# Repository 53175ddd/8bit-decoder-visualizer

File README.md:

# 8bit-decoder-visualizer

基板イメージ

動作イメージ（YouTube に飛びます）

## 部品表

| 部品番号 | 部品名 | 個数 | リンク |
|:----|:----|----:|:----|
| C1 | 0.1uF 1608M | 1 | [113374](<https://akizukidenshi.com/catalog/g/g113374/>) |
| D1 ~ D8 | LED 5mm | 8 | [112605](<https://akizukidenshi.com/catalog/g/g112605/>) |
| D9 ~ D16 | 1N4148W SOD-123F | 8 | [g116985](<https://akizukidenshi.com/catalog/g/g116985/>) |
| R1 ~ R8 | 1kΩ 1608M | 8 | [130351](<https://akizukidenshi.com/catalog/g/g130351/>) |
| R9 ~ R12 | 10kΩ 1608M | 4 | [130355](<https://akizukidenshi.com/catalog/g/g130355/>) |
| SW1 ~ SW8 | SPDT トグルスイッチ | 8 | [100300](<https://akizukidenshi.com/catalog/g/g100300/>) |
| U1 ~ U6 | 7 セグメント LED モジュール | 6 | [110360](<https://akizukidenshi.com/catalog/g/g110360/>) |
| U7 | 74HC595 | 1 | [131760](<https://akizukidenshi.com/catalog/g/g131760/>) |
| U8 | Seeed XIAO | 1 | [117044](<https://akizukidenshi.com/catalog/g/g117044/>) |

---

<a href="https://github.com/53175ddd/8bit-decoder-visualizer">This work</a> is licensed under <a href="https://creativecommons.org/licenses/by-sa/4.0/">CC BY-SA 4.0</a></br>

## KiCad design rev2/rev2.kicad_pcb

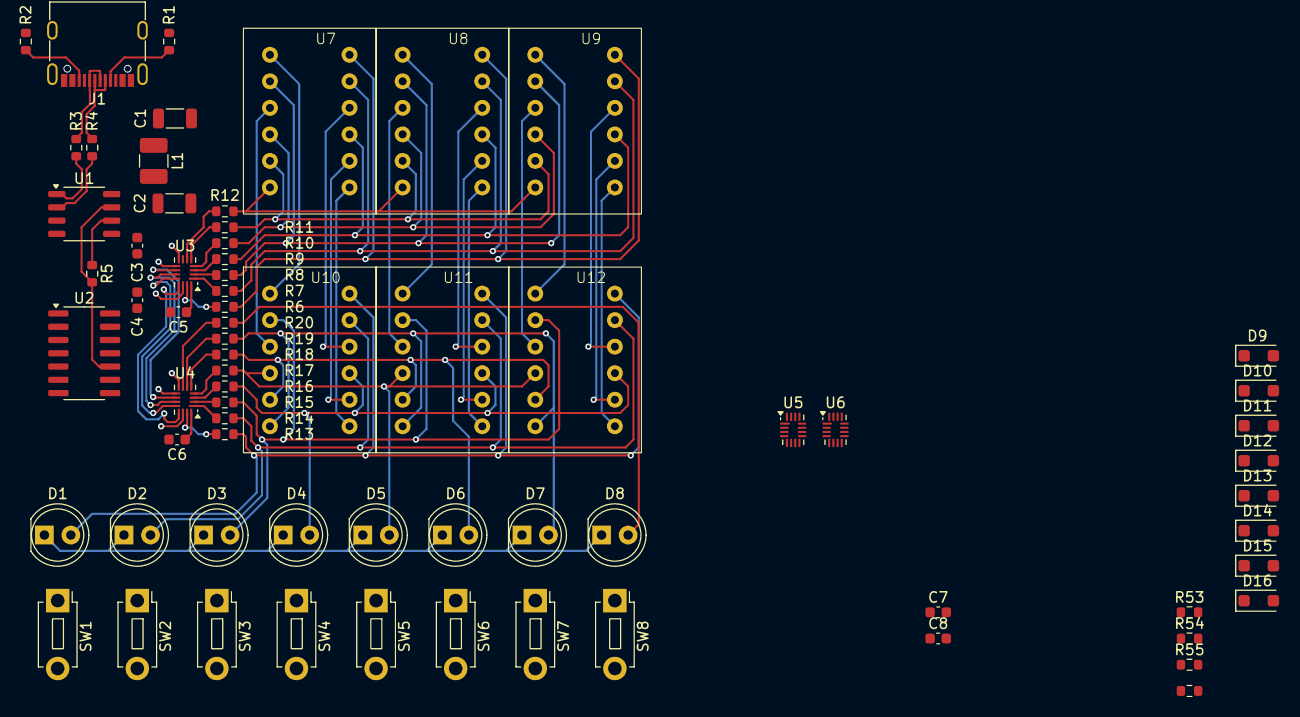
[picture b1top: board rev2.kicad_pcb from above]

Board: 2 copper layers, 70 parts (0 on the bottom side), 78 nets.

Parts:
C1, C2: 10uF; L_1206_3216Metric
C3, C4, C5, C6, C7, C8: 0.1uF; C_0603_1608Metric
D1, D2, D3, D4, D5, D6, D7, D8: LED; LED_D5.0mm
D9, D10, D11, D12, D13, D14, D15, D16: D; D_SOD-123F
J1: USB_C_Receptacle_USB2.0_14P; USB_C_Receptacle_G-Switch_GT-USB-7010ASV
L1: 1.5uH; L_1210_3225Metric_Pad1.42x2.65mm_HandSolder
R1, R2: 5.1k; R_0603_1608Metric
R3, R4: 22; R_0603_1608Metric
R5, R6, R7, R8, R9, R10, R11, R12, R13, R14, R15, R16, R17, R18, R19, R20: 1k; R_0603_1608Metric
R53, R54, R55, R56: 10k; R_0603_1608Metric
SW1, SW2, SW3, SW4, SW5, SW6, SW7, SW8: SW_Push; SW_PUSH_1P1T_6x3.5mm_H4.3_APEM_MJTP1243
U1: CH340N; SOP-8_3.9x4.9mm_P1.27mm
U2: ATtiny1604-SS; SOIC-14_3.9x8.7mm_P1.27mm
U3, U4, U5, U6: 74HC595; UQFN-16_1.8x2.6mm_P0.4mm
U7, U8, U9, U10, U11, U12: C-2570SR

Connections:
+5V: C2.1, C3.1, C4.1, C5.1, C6.1, C7.1, C8.1, L1.2, R53.1, R54.1, R55.1, R56.1, U1.5 (VCC), U2.1 (VCC), U3.16 (VCC), U4.16 (VCC), U5.16 (VCC), U6.16 (VCC)
/DN: R4.2, U1.2 (UD-)
/DP: R3.2, U1.1 (UD+)
/HC595_CLEAR: U3.10 (~SRCLR), U4.10 (~SRCLR), U5.10 (~SRCLR), U6.10 (~SRCLR)
/HC595_CLOCK: U3.11 (SRCLK), U4.11 (SRCLK), U5.11 (SRCLK), U6.11 (SRCLK)
/HC595_EN: U3.13 (~OE), U4.13 (~OE), U5.13 (~OE), U6.13 (~OE)
/HC595_LATCH: U3.12 (RCLK), U4.12 (RCLK), U5.12 (RCLK), U6.12 (RCLK)
/READ_0: R53.2, SW1.2, SW5.2
/READ_1: R54.2, SW2.2, SW6.2
/READ_2: R55.2, SW3.2, SW7.2
/READ_3: R56.2, SW4.2, SW8.2
/SCAN_0: D9.1 (K), D10.1 (K), D11.1 (K), D12.1 (K)
/SCAN_1: D13.1 (K), D14.1 (K), D15.1 (K), D16.1 (K)
/SOURCE_1A: R6.2, U7.12 (ROW1), U8.12 (ROW1), U9.12 (ROW1)
/SOURCE_1B: R7.2, U7.11 (ROW2), U8.11 (ROW2), U9.11 (ROW2)
/SOURCE_1C: R8.2, U7.2 (ROW3), U8.2 (ROW3), U9.2 (ROW3)
/SOURCE_1D: R9.2, U7.9 (ROW4), U8.9 (ROW4), U9.9 (ROW4)
/SOURCE_1E: R10.2, U7.4 (ROW5), U8.4 (ROW5), U9.4 (ROW5)
/SOURCE_1F: R11.2, U7.5 (ROW6), U8.5 (ROW6), U9.5 (ROW6)
/SOURCE_1G: R12.2, U7.6 (ROW7), U8.6 (ROW7), U9.6 (ROW7)
/SOURCE_2A: D1.2 (A), R13.2, U10.12 (ROW1), U11.12 (ROW1), U12.12 (ROW1)
/SOURCE_2B: D2.2 (A), R14.2, U10.11 (ROW2), U11.11 (ROW2), U12.11 (ROW2)
/SOURCE_2C: D3.2 (A), R15.2, U10.2 (ROW3), U11.2 (ROW3), U12.2 (ROW3)
/SOURCE_2D: D4.2 (A), R16.2, U10.9 (ROW4), U11.9 (ROW4), U12.9 (ROW4)
/SOURCE_2E: D5.2 (A), R17.2, U10.4 (ROW5), U11.4 (ROW5), U12.4 (ROW5)
/SOURCE_2F: D6.2 (A), R18.2, U10.5 (ROW6), U11.5 (ROW6), U12.5 (ROW6)
/SOURCE_2G: D7.2 (A), R19.2, U10.6 (ROW7), U11.6 (ROW7), U12.6 (ROW7)
/SOURCE_2H: D8.2 (A), R20.2
/UPDI: R5.2, U1.7 (RXD), U2.10 (~RESET/PA0)
/USB_PLUG_DN: J1.A7 (D-), J1.B7 (D-), R4.1
/USB_PLUG_DP: J1.A6 (D+), J1.B6 (D+), R3.1
GND: C1.2, C2.2, C3.2, C4.2, C5.2, C6.2, C7.2, C8.2, J1.A1 (GND), J1.A12 (GND), J1.B1 (GND), J1.B12 (GND), J1.S1 (SHIELD), R1.2, R2.2, U1.3 (GND), U2.14 (GND), U3.8 (GND), U4.8 (GND), U5.8 (GND), U6.8 (GND)
unnamed: D1.1 (K), D2.1 (K), D3.1 (K), D4.1 (K), D5.1 (K), D6.1 (K), D7.1 (K), D8.1 (K)
unnamed: D9.2 (A), SW1.1
unnamed: D10.2 (A), SW2.1
unnamed: D11.2 (A), SW3.1
unnamed: D12.2 (A), SW4.1
unnamed: D13.2 (A), SW5.1
unnamed: D14.2 (A), SW6.1
unnamed: D15.2 (A), SW7.1
unnamed: D16.2 (A), SW8.1
unnamed: J1.A5 (CC1), R1.1
unnamed: J1.B5 (CC2), R2.1
unnamed: U7.1 (COL1), U10.1 (COL1)
unnamed: U7.3 (COL2), U10.3 (COL2)
unnamed: U7.10 (COL3), U10.10 (COL3)
unnamed: U7.7 (COL4), U10.7 (COL4)
unnamed: U7.8 (COL5), U10.8 (COL5)
unnamed: U8.1 (COL1), U11.1 (COL1)
unnamed: U8.3 (COL2), U11.3 (COL2)
unnamed: U8.10 (COL3), U11.10 (COL3)
unnamed: U8.7 (COL4), U11.7 (COL4)
unnamed: U8.8 (COL5), U11.8 (COL5)
unnamed: U9.1 (COL1), U12.1 (COL1)
unnamed: U9.3 (COL2), U12.3 (COL2)
unnamed: U9.10 (COL3), U12.10 (COL3)
unnamed: U9.7 (COL4), U12.7 (COL4)
unnamed: U9.8 (COL5), U12.8 (COL5)
unnamed: R5.1, U1.6 (TXD)
unnamed: R6.1, U3.15 (QA)
unnamed: R7.1, U3.1 (QB)
unnamed: R8.1, U3.2 (QC)
unnamed: R9.1, U3.3 (QD)
unnamed: R10.1, U3.4 (QE)
unnamed: R11.1, U3.5 (QF)
unnamed: R12.1, U3.6 (QG)
unnamed: U3.9 (QH'), U4.14 (SER)
unnamed: R13.1, U4.15 (QA)
unnamed: R14.1, U4.1 (QB)
unnamed: R15.1, U4.2 (QC)
unnamed: R16.1, U4.3 (QD)
unnamed: R17.1, U4.4 (QE)
unnamed: R18.1, U4.5 (QF)
unnamed: R19.1, U4.6 (QG)
unnamed: U4.9 (QH'), U5.14 (SER)
unnamed: R20.1, U4.7 (QH)
unnamed: U5.9 (QH'), U6.14 (SER)
VBUS: C1.1, J1.A4 (VBUS), J1.A9 (VBUS), J1.B4 (VBUS), J1.B9 (VBUS), L1.1

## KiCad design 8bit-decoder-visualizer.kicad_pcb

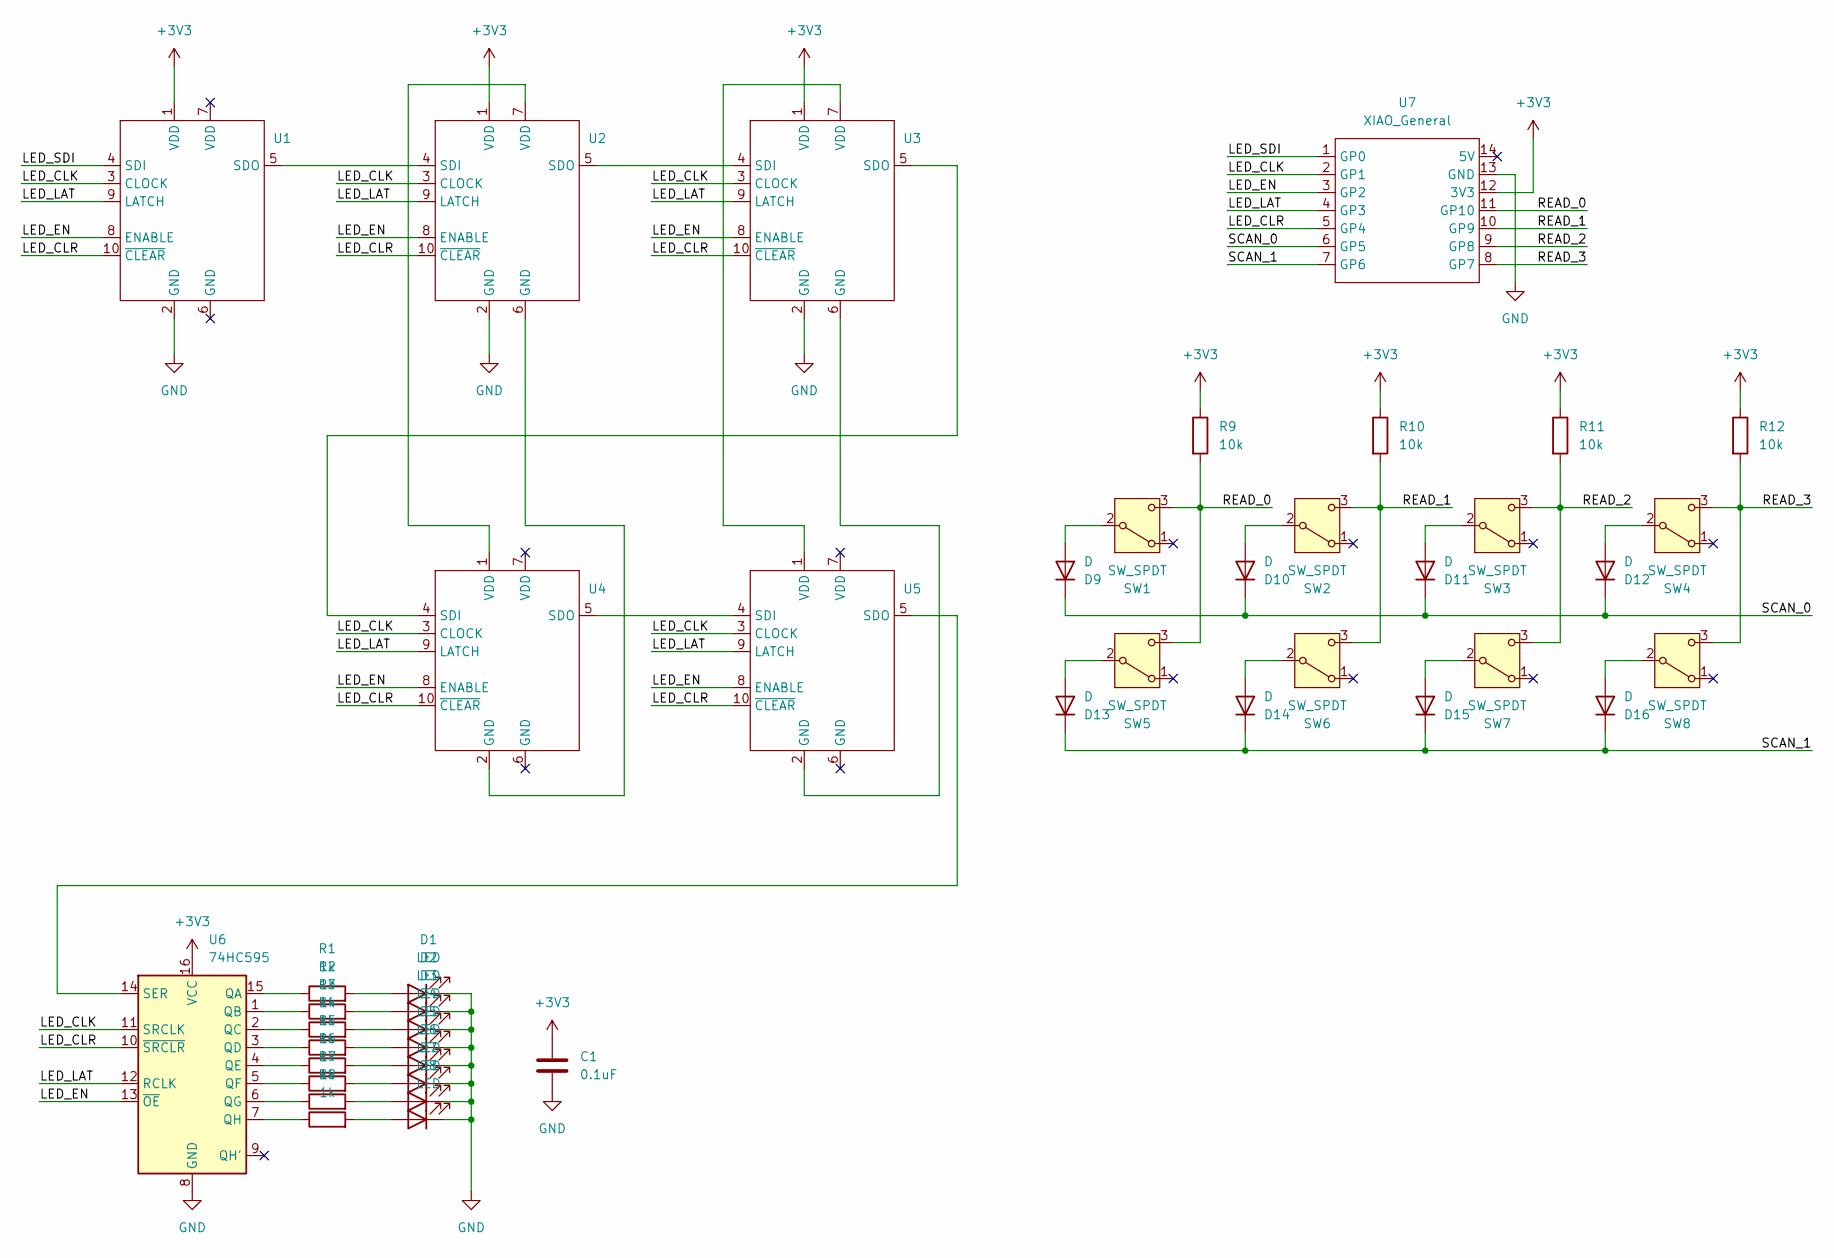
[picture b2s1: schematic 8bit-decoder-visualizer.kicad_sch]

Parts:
C1: 0.1uF; C_0603_1608Metric
D1, D2, D3, D4, D5, D6, D7, D8: LED; LED_D5.0mm
D9, D10, D11, D12, D13, D14, D15, D16: D; D_SOD-123F
R1, R2, R3, R4, R5, R6, R7, R8: 1k; R_0603_1608Metric
R9, R10, R11, R12: 10k; R_0603_1608Metric
SW1, SW2, SW3, SW4, SW5, SW6, SW7, SW8: SW_SPDT; SW_SPDT_100300
U1, U2, U3, U4, U5: LED Display Module; LED_Display_Module
U6: 74HC595; DIP-16_W7.62mm
U7: XIAO_General; XIAO_ESP32_C3

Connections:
+3V3: C1.1, R9.1, R10.1, R11.1, R12.1, U1.1 (VDD), U2.1 (VDD), U3.1 (VDD), U6.16 (VCC), U7.12 (3V3)
/LED_CLK: U1.3 (CLOCK), U2.3 (CLOCK), U3.3 (CLOCK), U4.3 (CLOCK), U5.3 (CLOCK), U6.11 (SRCLK), U7.2 (GP1)
/LED_CLR: U1.10 (~CLEAR), U2.10 (~CLEAR), U3.10 (~CLEAR), U4.10 (~CLEAR), U5.10 (~CLEAR), U6.10 (~SRCLR), U7.5 (GP4)
/LED_EN: U1.8 (ENABLE), U2.8 (ENABLE), U3.8 (ENABLE), U4.8 (ENABLE), U5.8 (ENABLE), U6.13 (~OE), U7.3 (GP2)
/LED_LAT: U1.9 (LATCH), U2.9 (LATCH), U3.9 (LATCH), U4.9 (LATCH), U5.9 (LATCH), U6.12 (RCLK), U7.4 (GP3)
/LED_SDI: U1.4 (SDI), U7.1 (GP0)
/READ_0: R9.2, SW1.3 (C), SW5.3 (C), U7.11 (GP10)
/READ_1: R10.2, SW2.3 (C), SW6.3 (C), U7.10 (GP9)
/READ_2: R11.2, SW3.3 (C), SW7.3 (C), U7.9 (GP8)
/READ_3: R12.2, SW4.3 (C), SW8.3 (C), U7.8 (GP7)
/SCAN_0: D9.1 (K), D10.1 (K), D11.1 (K), D12.1 (K), U7.6 (GP5)
/SCAN_1: D13.1 (K), D14.1 (K), D15.1 (K), D16.1 (K), U7.7 (GP6)
GND: C1.2, D1.1 (K), D2.1 (K), D3.1 (K), D4.1 (K), D5.1 (K), D6.1 (K), D7.1 (K), D8.1 (K), U1.2 (GND), U2.2 (GND), U3.2 (GND), U6.8 (GND), U7.13 (GND)
unnamed: D1.2 (A), R1.2
unnamed: D2.2 (A), R2.2
unnamed: D3.2 (A), R3.2
unnamed: D4.2 (A), R4.2
unnamed: D5.2 (A), R5.2
unnamed: D6.2 (A), R6.2
unnamed: D7.2 (A), R7.2
unnamed: D8.2 (A), R8.2
unnamed: D9.2 (A), SW1.2 (B)
unnamed: D10.2 (A), SW2.2 (B)
unnamed: D11.2 (A), SW3.2 (B)
unnamed: D12.2 (A), SW4.2 (B)
unnamed: D13.2 (A), SW5.2 (B)
unnamed: D14.2 (A), SW6.2 (B)
unnamed: D15.2 (A), SW7.2 (B)
unnamed: D16.2 (A), SW8.2 (B)
unnamed: U1.5 (SDO), U2.4 (SDI)
unnamed: U2.6 (GND), U4.2 (GND)
unnamed: U2.5 (SDO), U3.4 (SDI)
unnamed: U2.7 (VDD), U4.1 (VDD)
unnamed: U3.6 (GND), U5.2 (GND)
unnamed: U3.5 (SDO), U4.4 (SDI)
unnamed: U3.7 (VDD), U5.1 (VDD)
unnamed: U4.5 (SDO), U5.4 (SDI)
unnamed: U5.5 (SDO), U6.14 (SER)
unnamed: R1.1, U6.15 (QA)
unnamed: R2.1, U6.1 (QB)
unnamed: R3.1, U6.2 (QC)
unnamed: R4.1, U6.3 (QD)
unnamed: R5.1, U6.4 (QE)
unnamed: R6.1, U6.5 (QF)
unnamed: R7.1, U6.6 (QG)
unnamed: R8.1, U6.7 (QH)

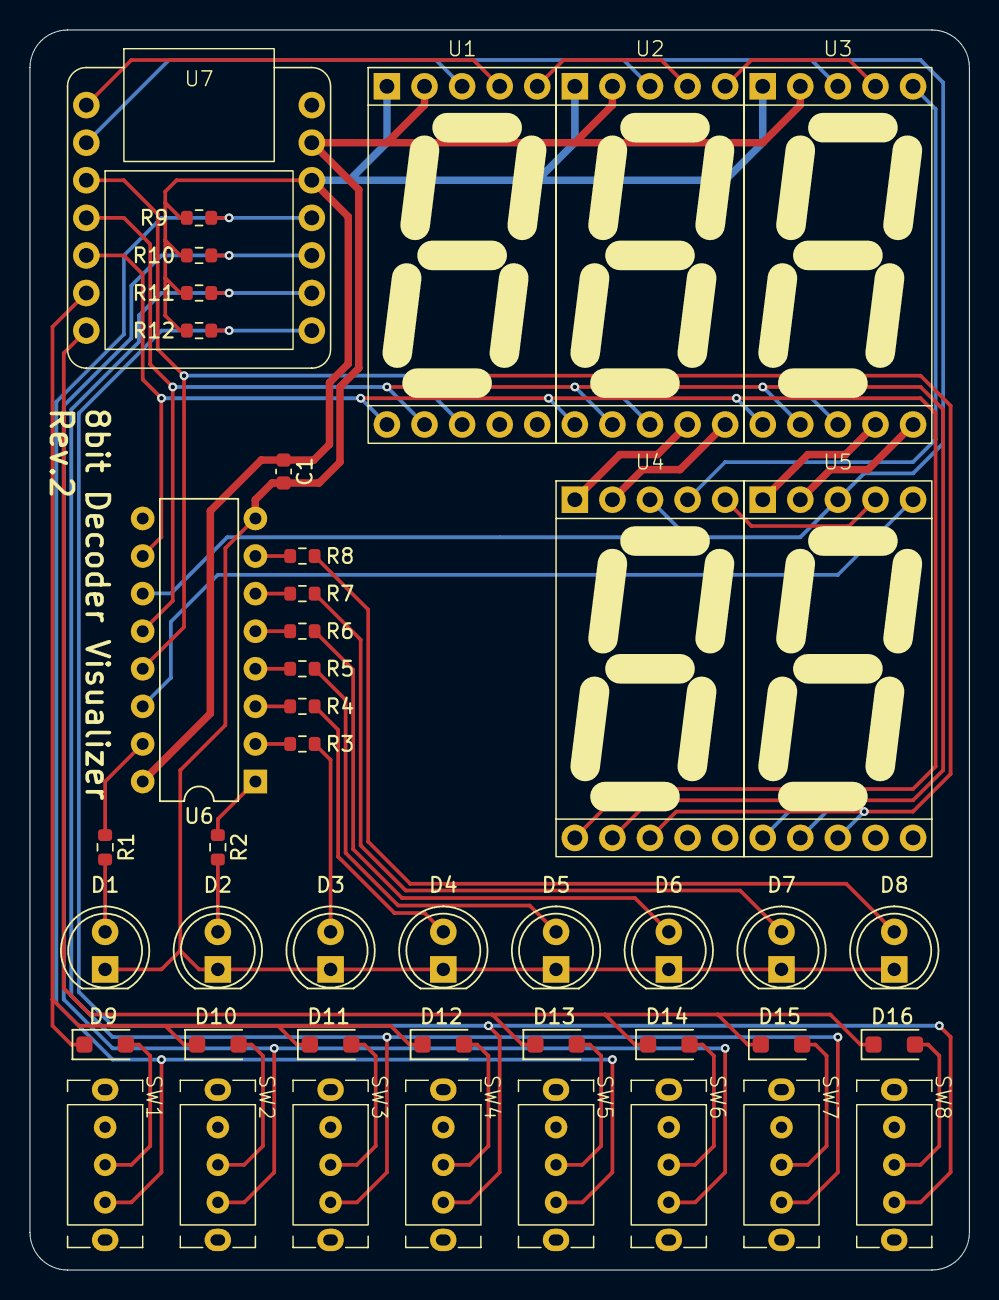
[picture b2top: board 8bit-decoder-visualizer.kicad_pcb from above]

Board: 2 copper layers, 63.5 x 83.8 mm, 44 parts (0 on the bottom side), 46 nets.

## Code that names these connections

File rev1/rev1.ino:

#define REV_1_1

#define LED_SDI  D0
#define LED_CLK  D1
#define LED_EN   D2
#define LED_LAT  D3
#define LED_CLR  D4
#define SCAN_0   D5
#define SCAN_1   D6
#define READ_0  D10
#define READ_1   D9
#define READ_2   D8
#define READ_3   D7

const uint8_t font[] = {0b11111100, 0b01100000, 0b11011010, 0b11110010, 0b01100110, 0b10110110, 0b10111110, 0b11100000, 0b11111110, 0b11110110, 0b11101110, 0b00111110, 0b00011010, 0b01111010, 0b10011110, 0b10001110};

const int8_t _scan[2] = {SCAN_0, SCAN_1};
const int8_t _read[4] = {READ_0, READ_1, READ_2, READ_3};


void init_io(void) {
  pinMode(LED_SDI, OUTPUT);
  pinMode(LED_CLK, OUTPUT);
  pinMode(LED_EN , OUTPUT);
  pinMode(LED_LAT, OUTPUT);
  pinMode(LED_CLR, OUTPUT);

  for(int8_t s = 0; s < 2; s++) {
    pinMode(_scan[s], OUTPUT);
    digitalWrite(_scan[s], HIGH);
  }

  for(int8_t r = 0; r < 4; r++) {
    pinMode(_read[r],  INPUT);
  }
}

void clear595(void) {
  digitalWrite(LED_CLR,  LOW);
  digitalWrite(LED_CLR, HIGH);
}

void send595(const uint8_t dat) {
  for(int8_t i = 0; i < 8; i++) {
    digitalWrite(LED_SDI, (dat >> i) & 1);
    digitalWrite(LED_CLK, HIGH);
    digitalWrite(LED_CLK, LOW);
  }
  digitalWrite(LED_SDI, LOW);
}

void latch595(void) {
  digitalWrite(LED_LAT, HIGH);
  digitalWrite(LED_LAT,  LOW);
}

uint8_t read_switch(void) {
  uint8_t res = 0;

  for(int8_t s = 0; s < 2; s++) digitalWrite(_scan[s], HIGH);

  for(int8_t s = 0; s < 2; s++) {
    digitalWrite(scan[s],  LOW);
    delayMicroseconds(20);

    for(int8_t r = 0; r < 4; r++) {
      res = (res << 1) + (digitalRead(_read[r]) == HIGH ? 0 : 1);
    }

    digitalWrite(_scan[s], HIGH);
  }

  return res;
}

void display(int8_t n) {
  static int8_t prev = -1;

  if(prev == n) return;
  prev = n;

#ifdef REV_1
  uint8_t vram[7] = {0};

  vram[0] = n;

  vram[6] = vram[0] / 100;
  vram[5] = (vram[0] / 10) % 10;
  vram[4] = vram[0] % 10;
  vram[3] = 0;
  vram[2] = vram[0] >> 4;
  vram[1] = vram[0] & 0x0F;

  vram[6] = font[vram[6]];
  vram[5] = font[vram[5]];
  vram[4] = font[vram[4]];
  vram[2] = font[vram[2]];
  vram[1] = font[vram[1]];

  if(vram[6] == font[0]) {
    vram[6] = 0;
    if(vram[5] == font[0]) {
      vram[5] = 0;
    }
  }

  if(vram[2] == font[0]) {
    vram[2] = 0;
  }
#endif

#ifdef REV_1_1
  uint8_t vram[6] = {0};

  vram[0] = n;

  vram[5] = vram[0] / 100;
  vram[4] = (vram[0] / 10) % 10;
  vram[3] = vram[0] % 10;
  vram[2] = vram[0] >> 4;
  vram[1] = vram[0] & 0x0F;

  vram[5] = font[vram[5]];
  vram[4] = font[vram[4]];
  vram[3] = font[vram[3]];
  vram[2] = font[vram[2]];
  vram[1] = font[vram[1]];

  if(vram[5] == font[0]) {
    vram[5] = 0;
    if(vram[4] == font[0]) {
      vram[4] = 0;
    }
  }

  if(vram[2] == font[0]) {
    vram[2] = 0;
  }
#endif

  for(int8_t i = 0; i < sizeof(vram); i++) {
    send595(vram[i]);
  }
  latch595();
}

void setup() {
  init_io();
  clear595();
}

void loop() {
  uint8_t n = read_switch();
  display(n);

  delay(25);
}

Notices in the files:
README.md:
https://mirrors.creativecommons.org/presskit/icons/cc.svg
https://mirrors.creativecommons.org/presskit/icons/by.svg
https://mirrors.creativecommons.org/presskit/icons/sa.svg
